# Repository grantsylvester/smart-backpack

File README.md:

# Smart Backpack
## Description
This repository houses the software and PCB design for the Smart Backpack being created by Purdue ECE49595SD Team 10E. The two main directories are:

- PCB
    - This directory houses the KiCad project files for our PCB.
- Software
    - This directory houses the PlatformIO project that has the code to be flashed onto the ESP32.

## Software To Do List
This is a list of modules in the software that we need to implement still:

- **main.c**
    - Integrate all components to run the main program in this file

- **gps.c** and **gps.h**
    - src and header files for GPS-related functions

- **imu.c** and **imu.h**
    - src and header files for IMU-related functions

- **rfid.c** and **rfid.h**
    - src and header files for RFID reader-related functions

- **sensors.c** and **sensors.h**
    - src and header files for all other sensors:
        - Water bottle sensors
        - Laptop detection pressure switches
        - Zipper state hall effect sensors
        - Haptic feedback motors
        - Back Cooling Fan (stretch goal)

- **app.c** and **app.h**
    - src and header files for Bluetooth connection and the web application.

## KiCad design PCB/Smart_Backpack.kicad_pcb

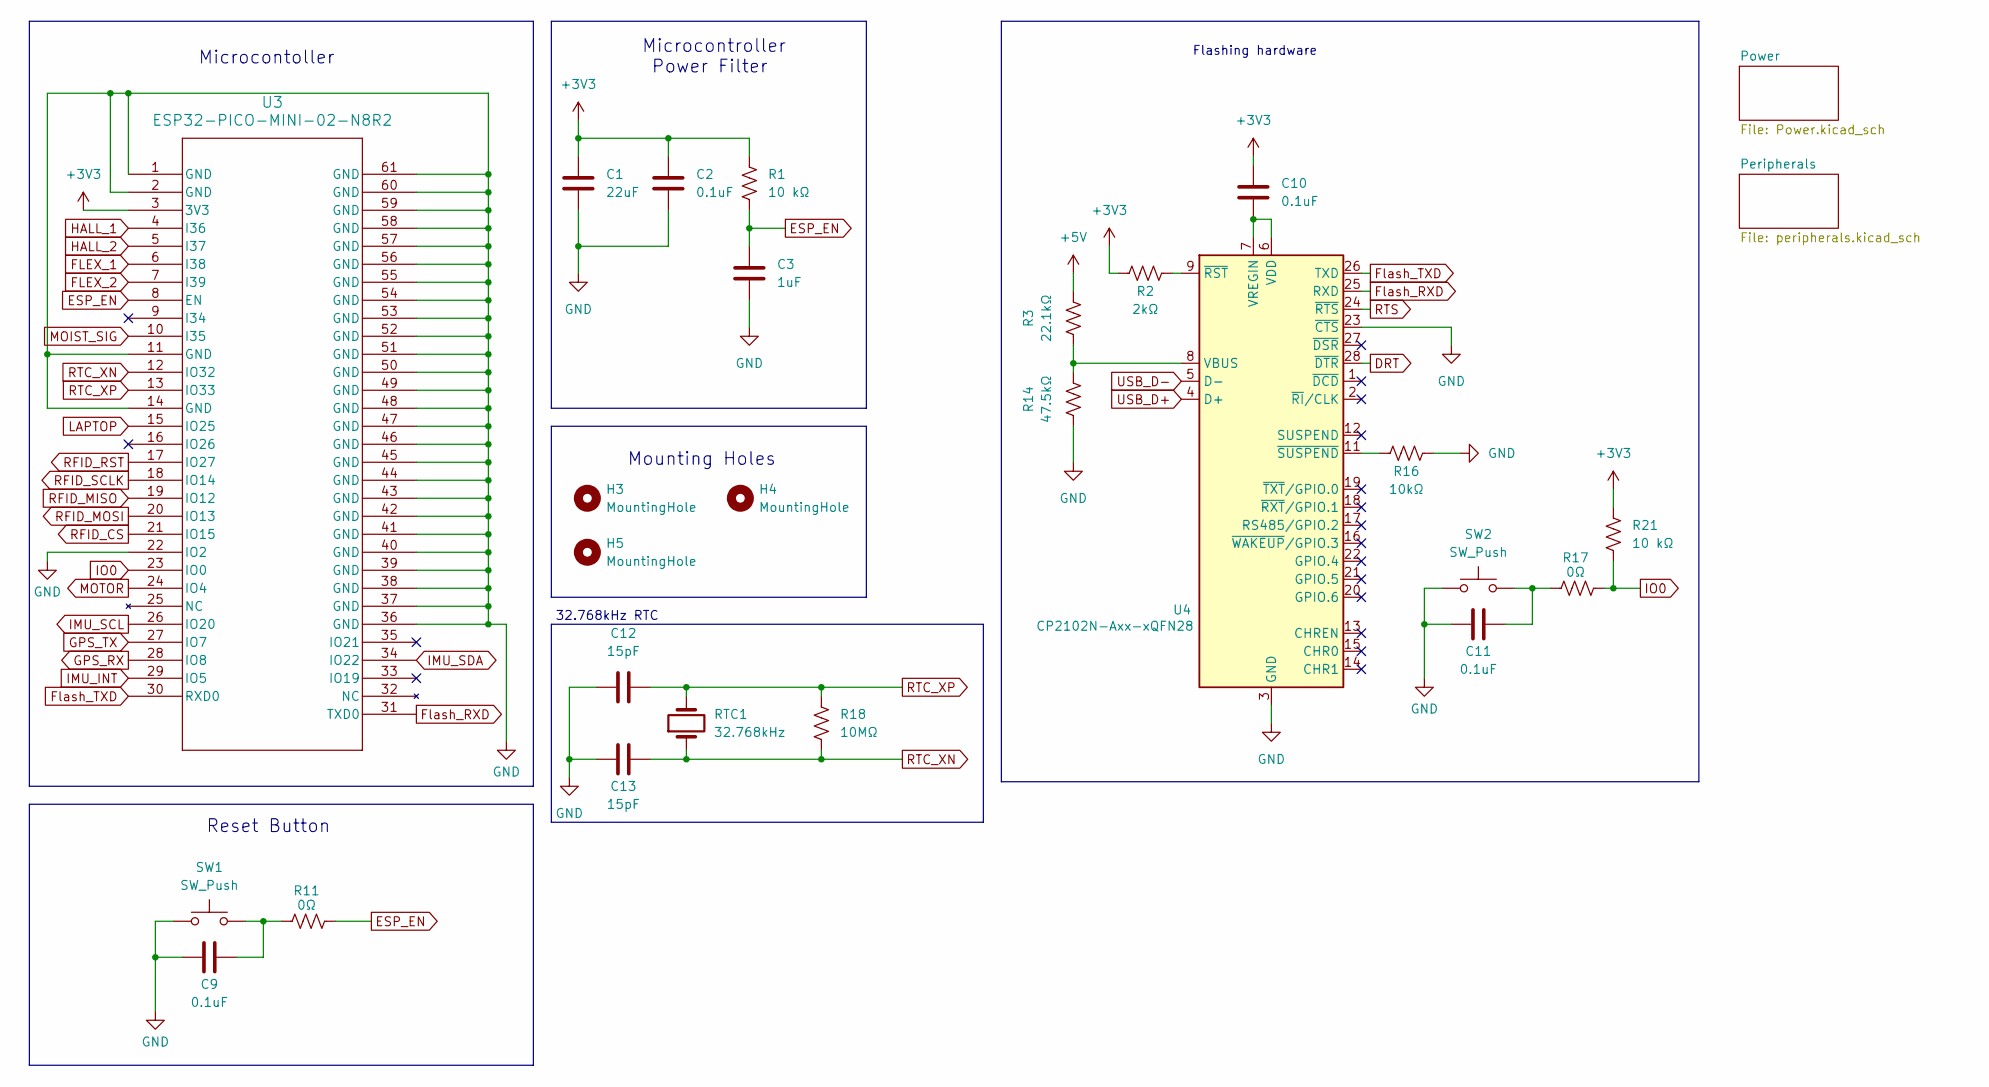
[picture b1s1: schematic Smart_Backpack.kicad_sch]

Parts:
C1: 22uF; C_1206_3216Metric_Pad1.33x1.80mm_HandSolder
C2, C9, C10, C11: 0.1uF; C_1206_3216Metric_Pad1.33x1.80mm_HandSolder
C3: 1uF; C_1206_3216Metric_Pad1.33x1.80mm_HandSolder
C12, C13: 15pF; C_1206_3216Metric_Pad1.33x1.80mm_HandSolder
H3, H4, H5: MountingHole; MountingHole_3mm
R1, R21: 10 kΩ; R_1206_3216Metric_Pad1.30x1.75mm_HandSolder
R2: 2kΩ; R_1206_3216Metric_Pad1.30x1.75mm_HandSolder
R3: 22.1kΩ; R_1206_3216Metric_Pad1.30x1.75mm_HandSolder
R11, R17: 0Ω; R_1206_3216Metric_Pad1.30x1.75mm_HandSolder
R14: 47.5kΩ; R_1206_3216Metric_Pad1.30x1.75mm_HandSolder
R16: 10kΩ; R_1206_3216Metric_Pad1.30x1.75mm_HandSolder
R18: 10MΩ; R_1206_3216Metric_Pad1.30x1.75mm_HandSolder
RTC1: 32.768kHz; XTAL_AB38T-32.768KHZ-B7
SW1, SW2: SW_Push; Shop_SMD_Button
U3: ESP32-PICO-MINI-02-N8R2; ESP32-PICO-MINI-02_EXP
U4: CP2102N-Axx-xQFN28; QFN-28-1EP_5x5mm_P0.5mm_EP3.35x3.35mm

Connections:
+3V3: C1.1, C2.1, C10.1, R1.1, R2.1, R21.1, U3.3 (3V3); also elsewhere on the board
+5V: R3.2; also elsewhere on the board
DRT: U4.28 (~DTR)
ESP_EN: C3.1, R1.2, R11.2, U3.8 (EN)
FLEX_1: U3.6 (I38); also elsewhere on the board
FLEX_2: U3.7 (I39); also elsewhere on the board
Flash_RXD: U3.31 (TXD0), U4.25 (RXD)
Flash_TXD: U3.30 (RXD0), U4.26 (TXD)
GND: C1.2, C2.2, C3.2, C9.2, C11.2, C12.1, C13.1, R14.1, R16.2, SW1.1, SW2.1, U3.1 (GND), U3.2 (GND), U3.11 (GND), U3.14 (GND), U3.22 (IO2), U3.36 (GND), U3.37 (GND), U3.38 (GND), U3.39 (GND), U3.40 (GND), U3.41 (GND), U3.42 (GND), U3.43 (GND), U3.44 (GND), U3.45 (GND), U3.46 (GND), U3.47 (GND), U3.48 (GND), U3.49 (GND), U3.50 (GND), U3.51 (GND), U3.52 (GND), U3.53 (GND), U3.54 (GND), U3.55 (GND), U3.56 (GND), U3.57 (GND), U3.58 (GND), U3.59 (GND), U3.60 (GND), U3.61 (GND), U4.3 (GND), U4.23 (~CTS), U4.29 (GND); also elsewhere on the board
GPS_RX: U3.28 (IO8); also elsewhere on the board
GPS_TX: U3.27 (IO7); also elsewhere on the board
HALL_1: U3.4 (I36); also elsewhere on the board
HALL_2: U3.5 (I37); also elsewhere on the board
IMU_INT: U3.29 (IO5); also elsewhere on the board
IMU_SCL: U3.26 (IO20); also elsewhere on the board
IMU_SDA: U3.34 (IO22); also elsewhere on the board
IO0: R17.2, R21.2, U3.23 (IO0)
LAPTOP: U3.15 (IO25); also elsewhere on the board
MOIST_SIG: U3.10 (I35); also elsewhere on the board
MOTOR: U3.24 (IO4); also elsewhere on the board
unnamed: C9.1, R11.1, SW1.2
unnamed: C11.1, R17.1, SW2.2
unnamed: R3.1, R14.2, U4.8 (VBUS)
unnamed: C10.2, U4.6 (VDD), U4.7 (VREGIN)
unnamed: R2.2, U4.9 (~RST)
unnamed: R16.1, U4.11 (~SUSPEND)
RFID_CS: U3.21 (IO15); also elsewhere on the board
RFID_MISO: U3.19 (IO12); also elsewhere on the board
RFID_MOSI: U3.20 (IO13); also elsewhere on the board
RFID_RST: U3.17 (IO27); also elsewhere on the board
RFID_SCLK: U3.18 (IO14); also elsewhere on the board
RTC_XN: C13.2, R18.2, RTC1.1, U3.12 (IO32)
RTC_XP: C12.2, R18.1, RTC1.2, U3.13 (IO33)
RTS: U4.24 (~RTS)
USB_D+: U4.4 (D+); also elsewhere on the board
USB_D-: U4.5 (D-); also elsewhere on the board

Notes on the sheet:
Mounting Holes
Microcontoller
32.768kHz RTC
Flashing hardware
Reset Button
Microcontroller Power Filter

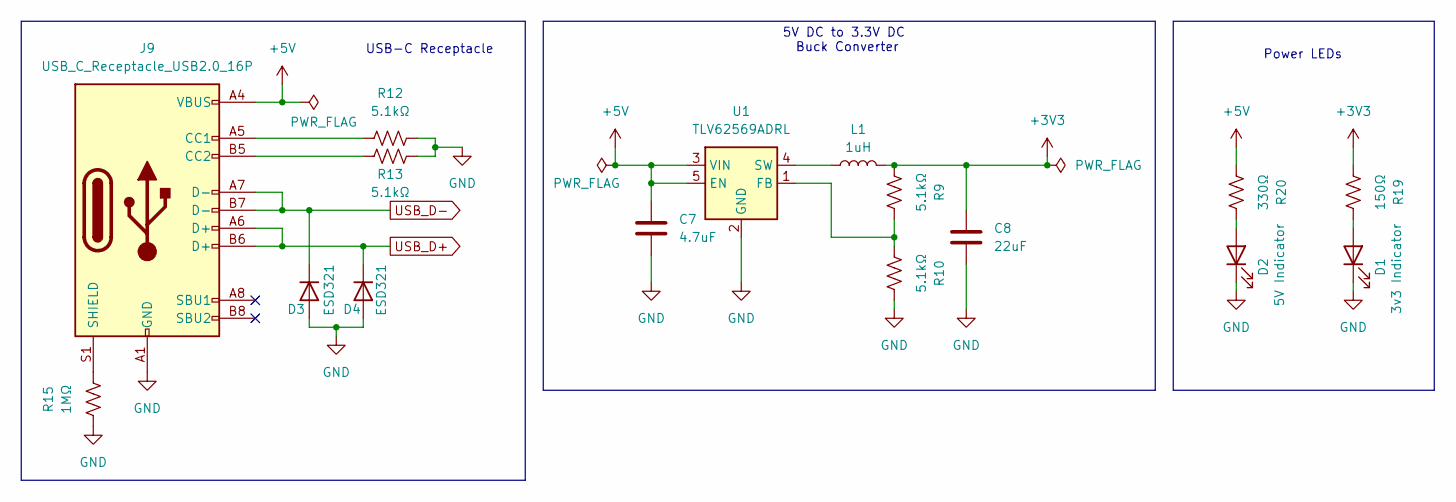
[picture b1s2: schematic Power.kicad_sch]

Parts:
C7: 4.7uF; C_1206_3216Metric_Pad1.33x1.80mm_HandSolder
C8: 22uF; C_1206_3216Metric_Pad1.33x1.80mm_HandSolder
D1: 3v3 Indicator; LED_0603_1608Metric_Pad1.05x0.95mm_HandSolder
D2: 5V Indicator; LED_0603_1608Metric_Pad1.05x0.95mm_HandSolder
D3, D4: ESD321; D_0402_1005Metric_Pad0.77x0.64mm_HandSolder
J9: USB_C_Receptacle_USB2.0_16P; USB_C_Receptacle_G-Switch_GT-USB-7010ASV
L1: 1uH; IND_BOURNS_SRN8040
R9, R10, R12, R13: 5.1kΩ; R_1206_3216Metric_Pad1.30x1.75mm_HandSolder
R15: 1MΩ; R_1206_3216Metric_Pad1.30x1.75mm_HandSolder
R19: 150Ω; R_1206_3216Metric_Pad1.30x1.75mm_HandSolder
R20: 330Ω; R_1206_3216Metric_Pad1.30x1.75mm_HandSolder
U1: TLV62569ADRL; SOT-563

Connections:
+3V3: C8.1, L1.2, R9.1, R19.1; also elsewhere on the board
+5V: C7.1, J9.A4 (VBUS), J9.A9 (VBUS), J9.B4 (VBUS), J9.B9 (VBUS), R20.1, U1.3 (VIN), U1.5 (EN); also elsewhere on the board
GND: C7.2, C8.2, D1.1 (K), D2.1 (K), D3.2 (A), D4.2 (A), J9.A1 (GND), J9.A12 (GND), J9.B1 (GND), J9.B12 (GND), R10.2, R12.2, R13.2, R15.1, U1.2 (GND); also elsewhere on the board
unnamed: D1.2 (A), R19.2
unnamed: D2.2 (A), R20.2
unnamed: J9.A5 (CC1), R12.1
unnamed: J9.B5 (CC2), R13.1
unnamed: J9.S1 (SHIELD), R15.2
unnamed: R9.2, R10.1, U1.1 (FB)
unnamed: L1.1, U1.4 (SW)
USB_D+: D4.1 (K), J9.A6 (D+), J9.B6 (D+); also elsewhere on the board
USB_D-: D3.1 (K), J9.A7 (D-), J9.B7 (D-); also elsewhere on the board

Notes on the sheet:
5V DC to 3.3V DC Buck Converter
Power LEDs
USB-C Receptacle

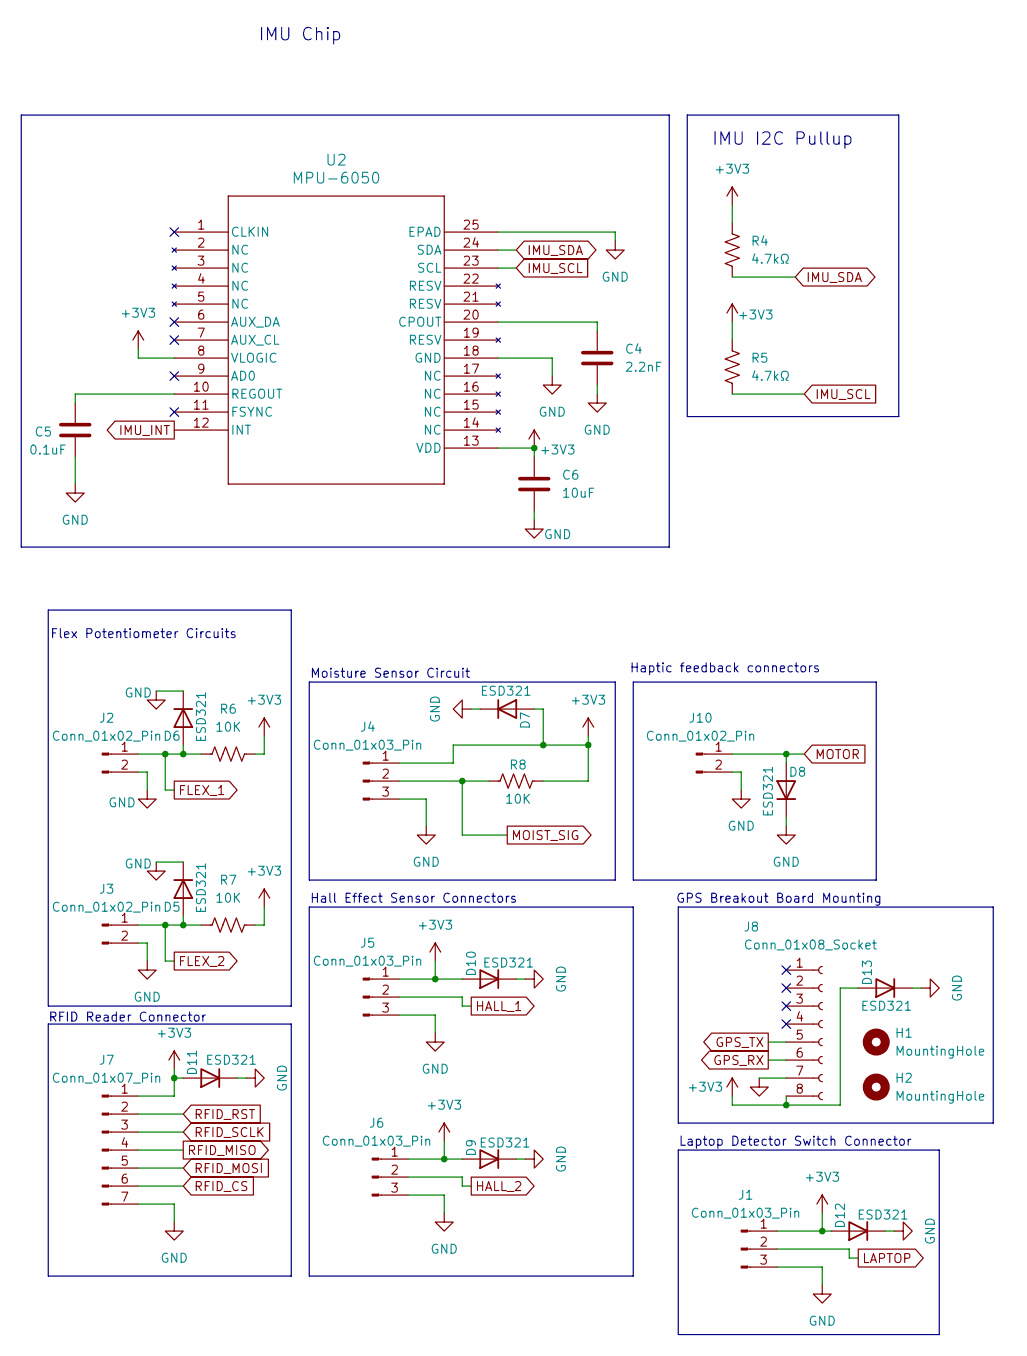
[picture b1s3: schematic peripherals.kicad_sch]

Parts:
C4: 2.2nF; C_1206_3216Metric_Pad1.33x1.80mm_HandSolder
C5: 0.1uF; C_1206_3216Metric_Pad1.33x1.80mm_HandSolder
C6: 10uF; C_1206_3216Metric_Pad1.33x1.80mm_HandSolder
D5, D6, D7, D8, D9, D10, D11, D12, D13: ESD321; D_0402_1005Metric_Pad0.77x0.64mm_HandSolder
H1, H2: MountingHole; MountingHole_2.2mm_M2
J1, J4, J5, J6: Conn_01x03_Pin; JST_VH_B3PS-VH_1x03_P3.96mm_Horizontal
J2, J3, J10: Conn_01x02_Pin; JST_VH_B2PS-VH_1x02_P3.96mm_Horizontal
J7: Conn_01x07_Pin; JST_VH_B7PS-VH_1x07_P3.96mm_Horizontal
J8: Conn_01x08_Socket; PinHeader_1x08_P2.54mm_Vertical
R4, R5: 4.7kΩ; R_1206_3216Metric_Pad1.30x1.75mm_HandSolder
R6, R7, R8: 10K; R_1206_3216Metric_Pad1.30x1.75mm_HandSolder
U2: MPU-6050; QFN24_4X4X0P9-0P5_TDK-L

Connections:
+3V3: C6.1, D7.2 (A), D9.2 (A), D10.2 (A), D11.2 (A), D12.2 (A), D13.2 (A), J1.1, J4.1, J5.1, J6.1, J7.1, J8.8, R4.1, R5.1, R6.2, R7.2, R8.2, U2.8 (VLOGIC), U2.13 (VDD); also elsewhere on the board
FLEX_1: D6.2 (A), J2.1, R6.1; also elsewhere on the board
FLEX_2: D5.2 (A), J3.1, R7.1; also elsewhere on the board
GND: C4.2, C5.2, C6.2, D5.1 (K), D6.1 (K), D7.1 (K), D8.1 (K), D9.1 (K), D10.1 (K), D11.1 (K), D12.1 (K), D13.1 (K), J1.3, J2.2, J3.2, J4.3, J5.3, J6.3, J7.7, J8.7, J10.2, U2.18 (GND), U2.25 (EPAD); also elsewhere on the board
GPS_RX: J8.6; also elsewhere on the board
GPS_TX: J8.5; also elsewhere on the board
HALL_1: J5.2; also elsewhere on the board
HALL_2: J6.2; also elsewhere on the board
IMU_INT: U2.12 (INT); also elsewhere on the board
IMU_SCL: R5.2, U2.23 (SCL); also elsewhere on the board
IMU_SDA: R4.2, U2.24 (SDA); also elsewhere on the board
LAPTOP: J1.2; also elsewhere on the board
MOIST_SIG: J4.2, R8.1; also elsewhere on the board
MOTOR: D8.2 (A), J10.1; also elsewhere on the board
unnamed: C4.1, U2.20 (CPOUT)
unnamed: C5.1, U2.10 (REGOUT)
RFID_CS: J7.6; also elsewhere on the board
RFID_MISO: J7.4; also elsewhere on the board
RFID_MOSI: J7.5; also elsewhere on the board
RFID_RST: J7.2; also elsewhere on the board
RFID_SCLK: J7.3; also elsewhere on the board

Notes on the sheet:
IMU I2C Pullup
Laptop Detector Switch Connector
GPS Breakout Board Mounting
RFID Reader Connector
Flex Potentiometer Circuits
Haptic feedback connectors
Moisture Sensor Circuit
Hall Effect Sensor Connectors
IMU Chip

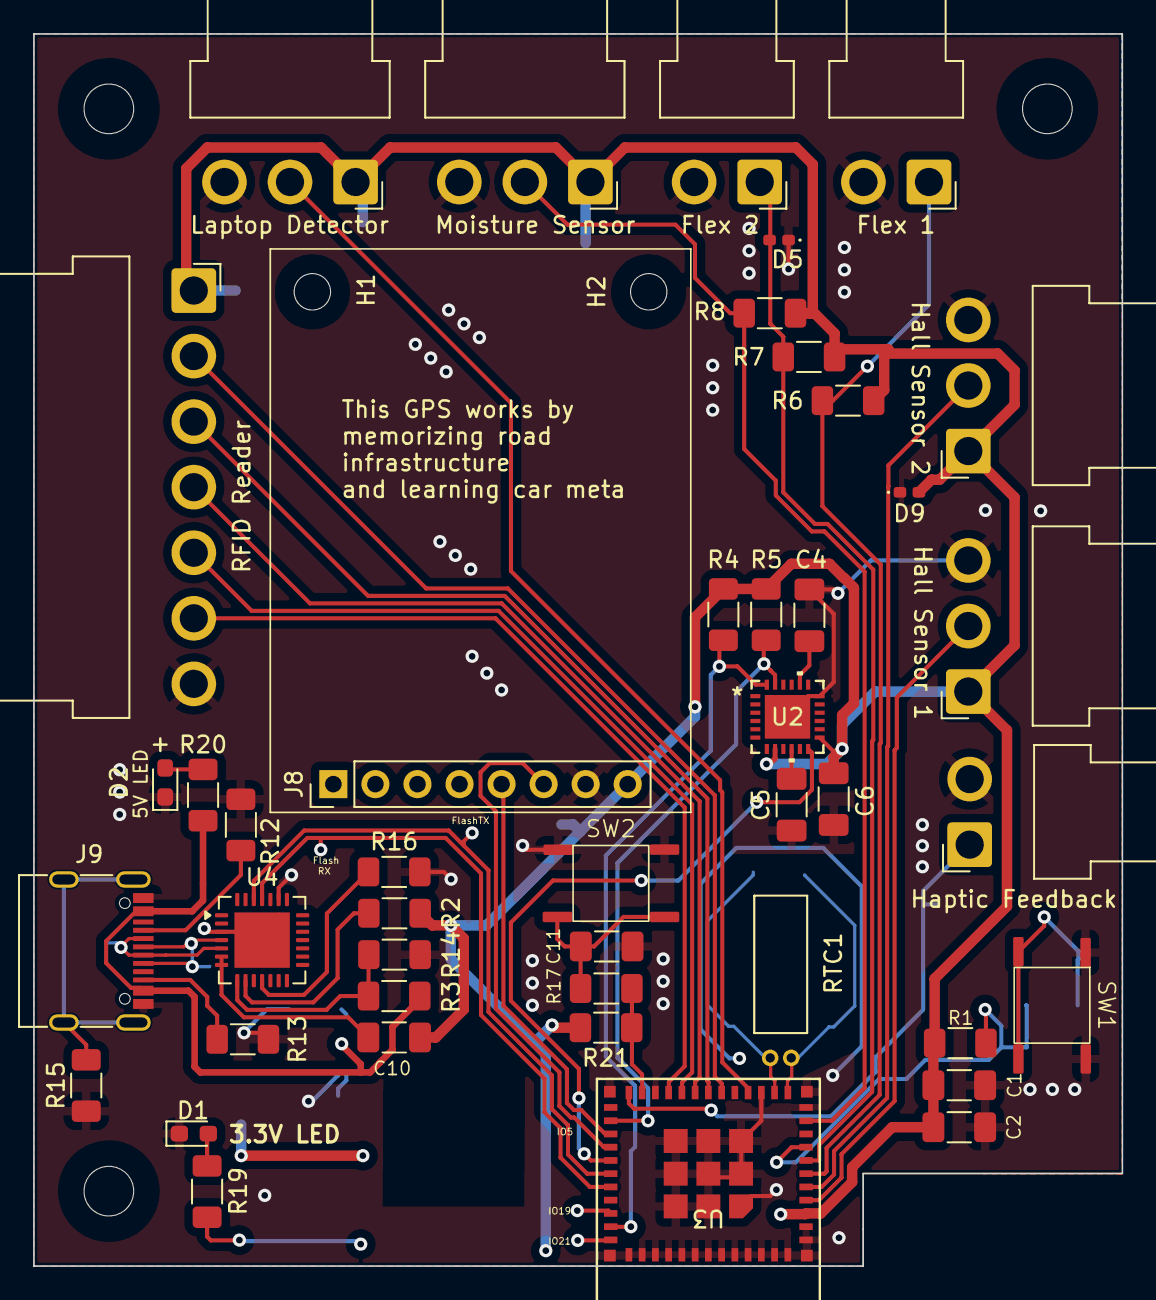
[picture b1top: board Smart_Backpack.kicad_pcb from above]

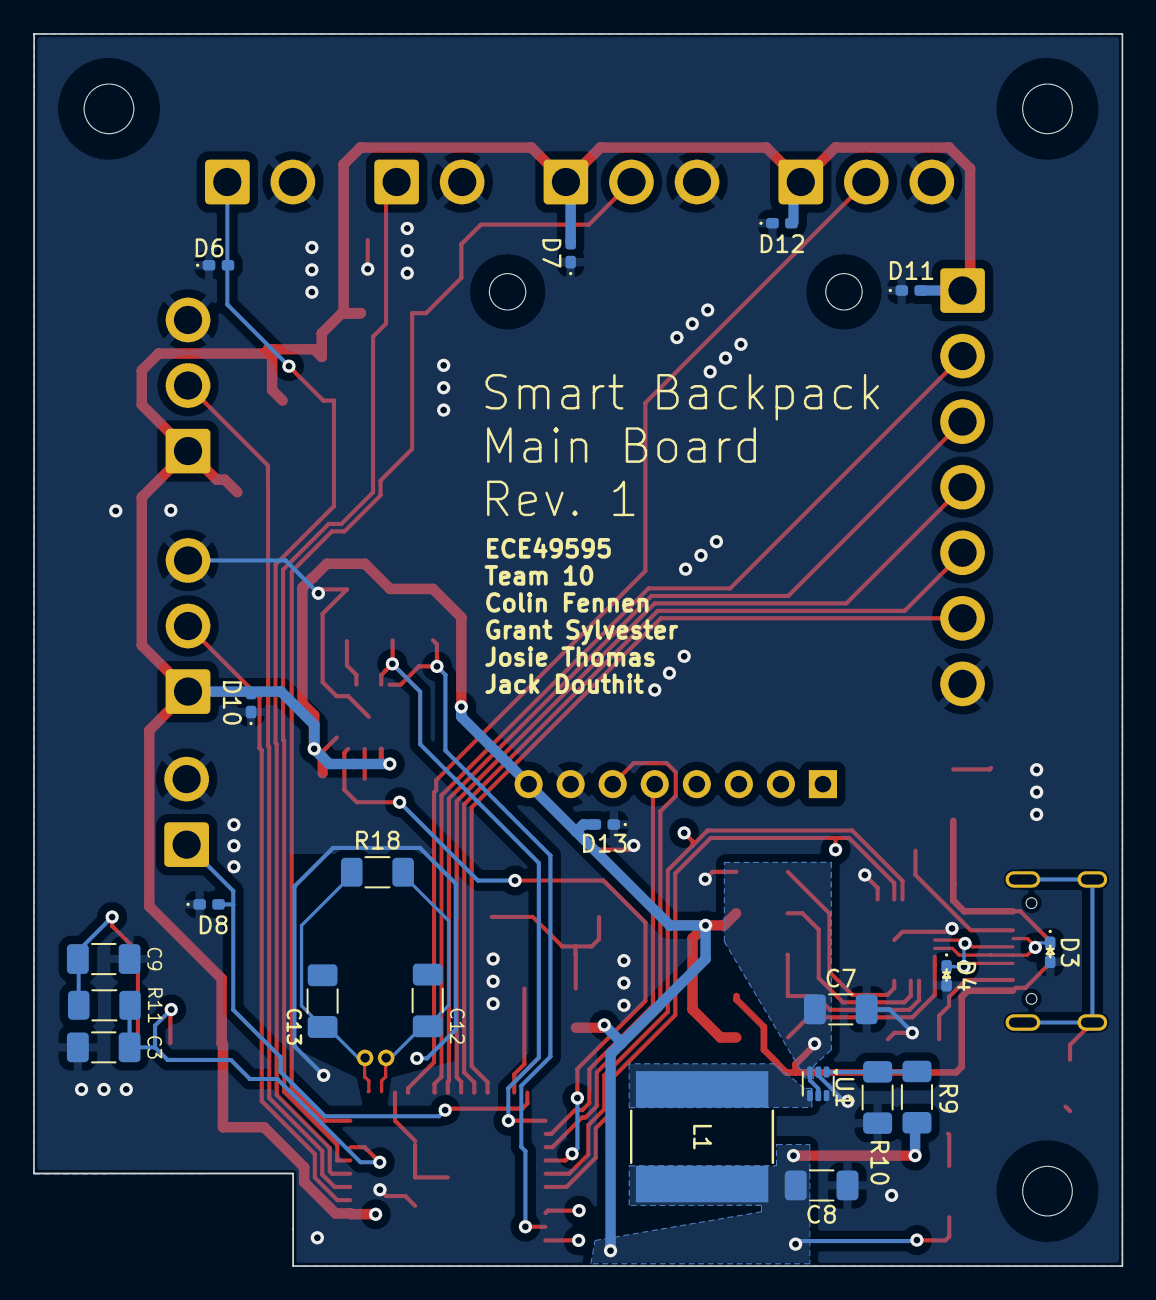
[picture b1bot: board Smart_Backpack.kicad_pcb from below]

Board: 2 copper layers, 65.8 x 74.4 mm, 70 parts (21 on the bottom side), 43 nets.

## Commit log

2026-01-22 create platformIO project
2026-01-22 create PCB folder
2026-01-23 Create temp
2026-01-23 Delete PCB/Smart Backpack PCB-backups directory
    I'm dumb and can just add the folder
2026-01-23 Delete PCB/Smart_Backpack-Backups directory
    I'm dumb and can just add the folder
2026-01-23 test
2026-01-23 jack test
2026-01-23 update README with organization
2026-01-23 Delete PCB/untitled.kicad_sch
    I hate this software
2026-01-26 Added IMU footprint/symbol
2026-01-26 update todo list
2026-01-27 New IMU symbol/footprint
2026-01-27 Just changed some ground pins to ground
2026-01-27 Added micro footprint
2026-01-28 work on IMU
2026-01-29 IMU done yay
2026-01-31 add connectors for off-board components
2026-02-06 She buck on my converter till I 3.3V DC
2026-02-07 add pressure button and R, C, and L footprints
2026-02-07 Work on adding on board flashing
2026-02-09 Updated to-do list
2026-02-10 Created push button footprint
2026-02-10 Added IO0 button
2026-02-11 add RTC and TX/RX signals
2026-02-12 add power indicator LEDs, connect peripherals
2026-02-14 lots of 'final' schematic updates. ERC is essentially clean, PCB design can begin
2026-02-14 Created BOM and added USBC footprint
2026-02-15 Finally PCB progress
2026-02-16 bit more PCB progress, added buttons and filter
2026-02-16 route IMU, fix MCU orientation, space GPS mounting
2026-02-17 place and route connectors, add edges
2026-02-17 PCB revision 1 is finished!!!!
2026-02-17 add ground vias, RTC protection, and mounting hole exclusion zones
2026-02-17 Some updates suggested by Ryan (The 1 sem senior design prof)
2026-02-18 Literally just added our names
2026-02-18 Added motors :pensive:
2026-02-18 add datasheets to schematic and silkscreen board label
2026-02-18 fix silkscreen for motor connector
2026-02-24 Alert: Fat inductor incoming
2026-02-25 fix edge cuts and route IMU_INT
2026-02-27 add esd protection and buck caps and move USB-C over edge
2026-03-03 PCB hopefully finished
2026-03-06 fix esd diode footprints
2026-03-06 Fixed all DRC
2026-03-06 Generated Gerbers
2026-03-07 Start of feedback implementation
2026-03-07 Implemented all feedback except buck converter
2026-03-08 This time for sure...
2026-03-09 add new feedback
2026-03-09 add one singular via
2026-03-10 fix power layout again
2026-03-13 PCB finished and ordered
